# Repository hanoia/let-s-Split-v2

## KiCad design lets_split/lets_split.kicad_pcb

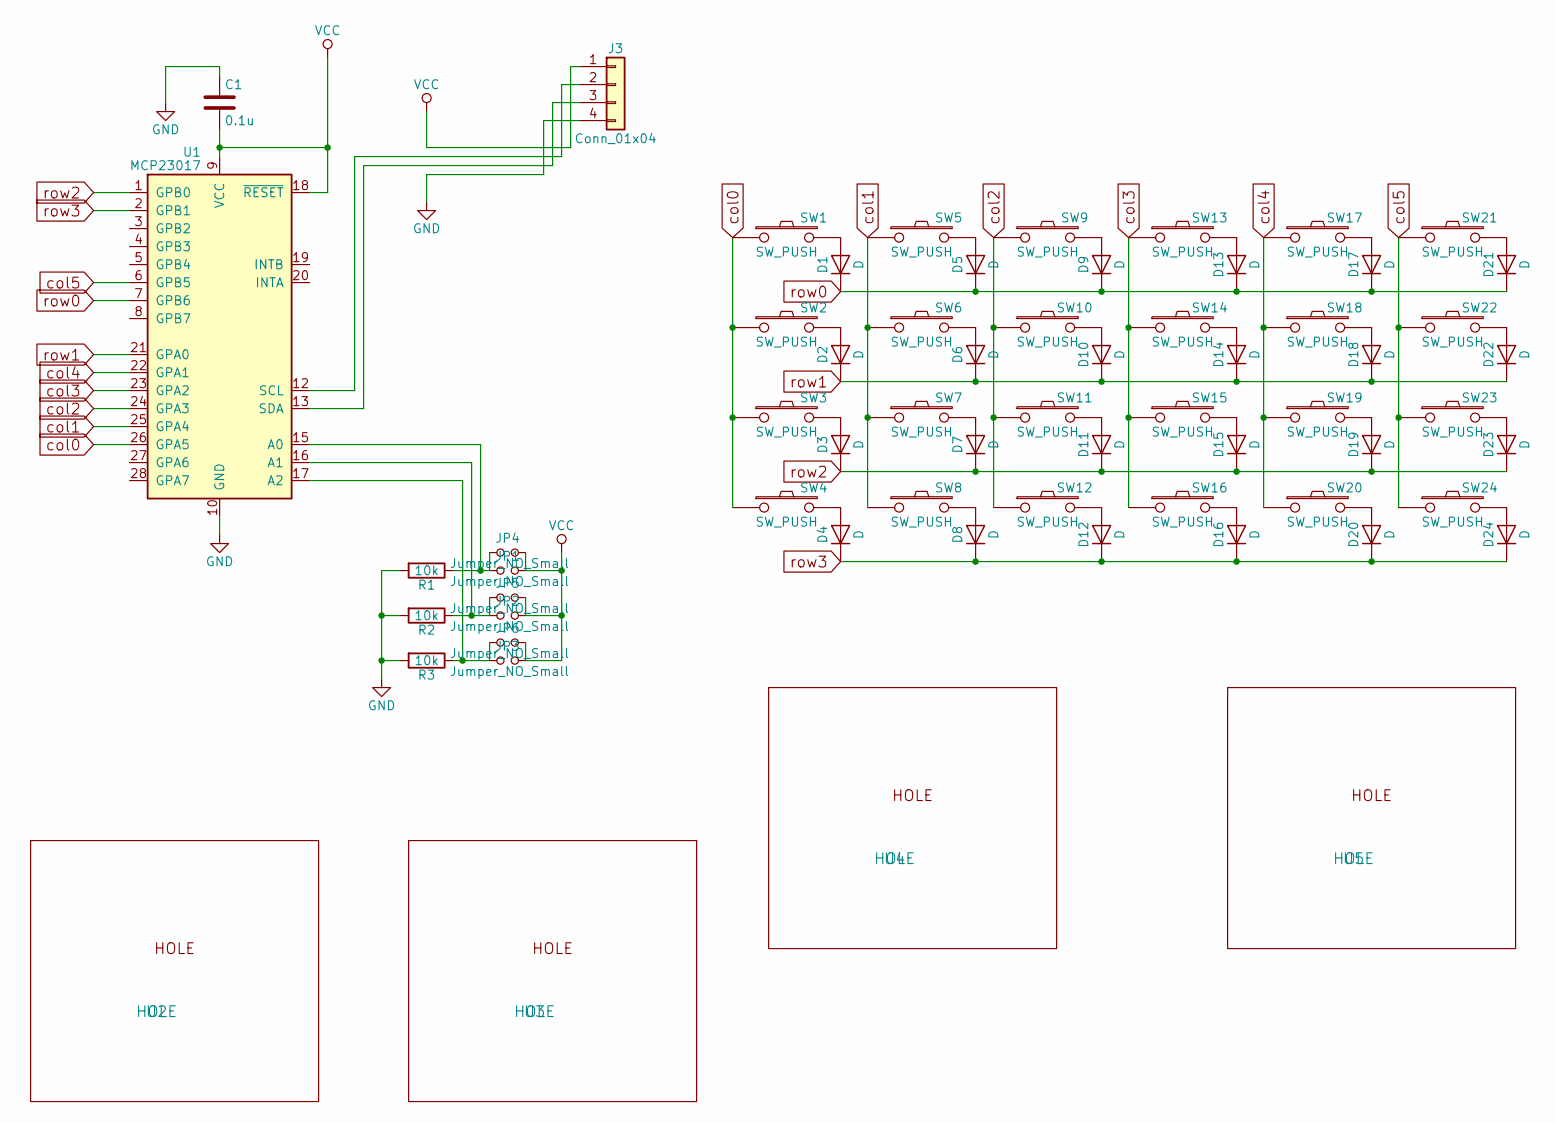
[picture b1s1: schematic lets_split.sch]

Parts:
C1: 0.1u; C_0603
D1, D2, D3, D4, D5, D6, D7, D8, D9, D10, D11, D12, D13, D14, D15, D16, D17, D18, D19, D20, D21, D22, D23, D24: D; D_SOD-123
J3: Conn_01x04; Pin_Header_Straight_1x04_Pitch2.54mm
JP1, JP2, JP3, JP4, JP5, JP6: Jumper_NO_Small; SolderJumper-2_P1.3mm_Open_Pad1.0x1.5mm
R1, R2, R3: 10k; R_0603
SW1, SW2, SW3, SW4, SW5, SW6, SW7, SW8, SW9, SW10, SW11, SW12, SW13, SW14, SW15, SW16, SW17, SW18, SW19, SW20, SW21, SW22, SW23, SW24: SW_PUSH; MXALPS_FLIP
U1: MCP23017; QFN-28-1EP_6x6mm_Pitch0.65mm
U2, U3, U4, U5: HOLE

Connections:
GND: C1.1, J3.4, R1.2, R2.2, R3.2, U1.10 (GND)
unnamed: D1.2 (A), SW1.2
unnamed: D2.2 (A), SW2.2
unnamed: D3.2 (A), SW3.2
unnamed: D4.2 (A), SW4.2
unnamed: D5.2 (A), SW5.2
unnamed: D6.2 (A), SW6.2
unnamed: D7.2 (A), SW7.2
unnamed: D8.2 (A), SW8.2
unnamed: D9.2 (A), SW9.2
unnamed: D10.2 (A), SW10.2
unnamed: D11.2 (A), SW11.2
unnamed: D12.2 (A), SW12.2
unnamed: D13.2 (A), SW13.2
unnamed: D14.2 (A), SW14.2
unnamed: D15.2 (A), SW15.2
unnamed: D16.2 (A), SW16.2
unnamed: D17.2 (A), SW17.2
unnamed: D18.2 (A), SW18.2
unnamed: D19.2 (A), SW19.2
unnamed: D20.2 (A), SW20.2
unnamed: D21.2 (A), SW21.2
unnamed: D22.2 (A), SW22.2
unnamed: D23.2 (A), SW23.2
unnamed: D24.2 (A), SW24.2
unnamed: J3.2, U1.12 (SCL)
unnamed: J3.3, U1.13 (SDA)
unnamed: JP1.1, JP4.1, R1.1, U1.15 (A0)
unnamed: JP2.1, JP5.1, R2.1, U1.16 (A1)
unnamed: JP3.1, JP6.1, R3.1, U1.17 (A2)
VCC: C1.2, J3.1, JP1.2, JP2.2, JP3.2, JP4.2, JP5.2, JP6.2, U1.9 (VCC), U1.18 (~RESET)
col0: SW1.1, SW2.1, SW3.1, SW4.1, U1.26 (GPA5)
col1: SW5.1, SW6.1, SW7.1, SW8.1, U1.25 (GPA4)
col2: SW9.1, SW10.1, SW11.1, SW12.1, U1.24 (GPA3)
col3: SW13.1, SW14.1, SW15.1, SW16.1, U1.23 (GPA2)
col4: SW17.1, SW18.1, SW19.1, SW20.1, U1.22 (GPA1)
col5: SW21.1, SW22.1, SW23.1, SW24.1, U1.6 (GPB5)
row0: D1.1 (K), D5.1 (K), D9.1 (K), D13.1 (K), D17.1 (K), D21.1 (K), U1.7 (GPB6)
row1: D2.1 (K), D6.1 (K), D10.1 (K), D14.1 (K), D18.1 (K), D22.1 (K), U1.21 (GPA0)
row2: D3.1 (K), D7.1 (K), D11.1 (K), D15.1 (K), D19.1 (K), D23.1 (K), U1.1 (GPB0)
row3: D4.1 (K), D8.1 (K), D12.1 (K), D16.1 (K), D20.1 (K), D24.1 (K), U1.2 (GPB1)

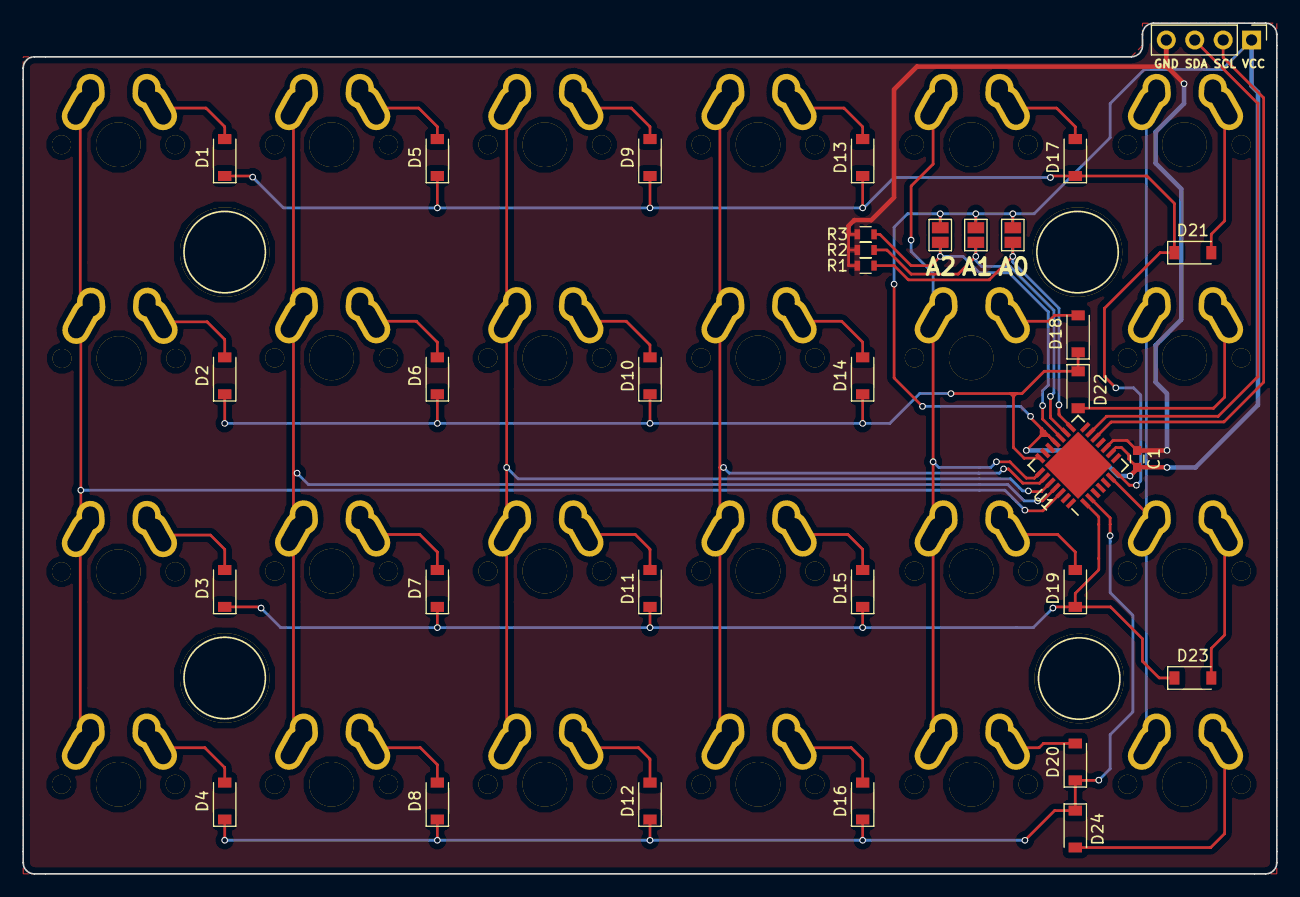
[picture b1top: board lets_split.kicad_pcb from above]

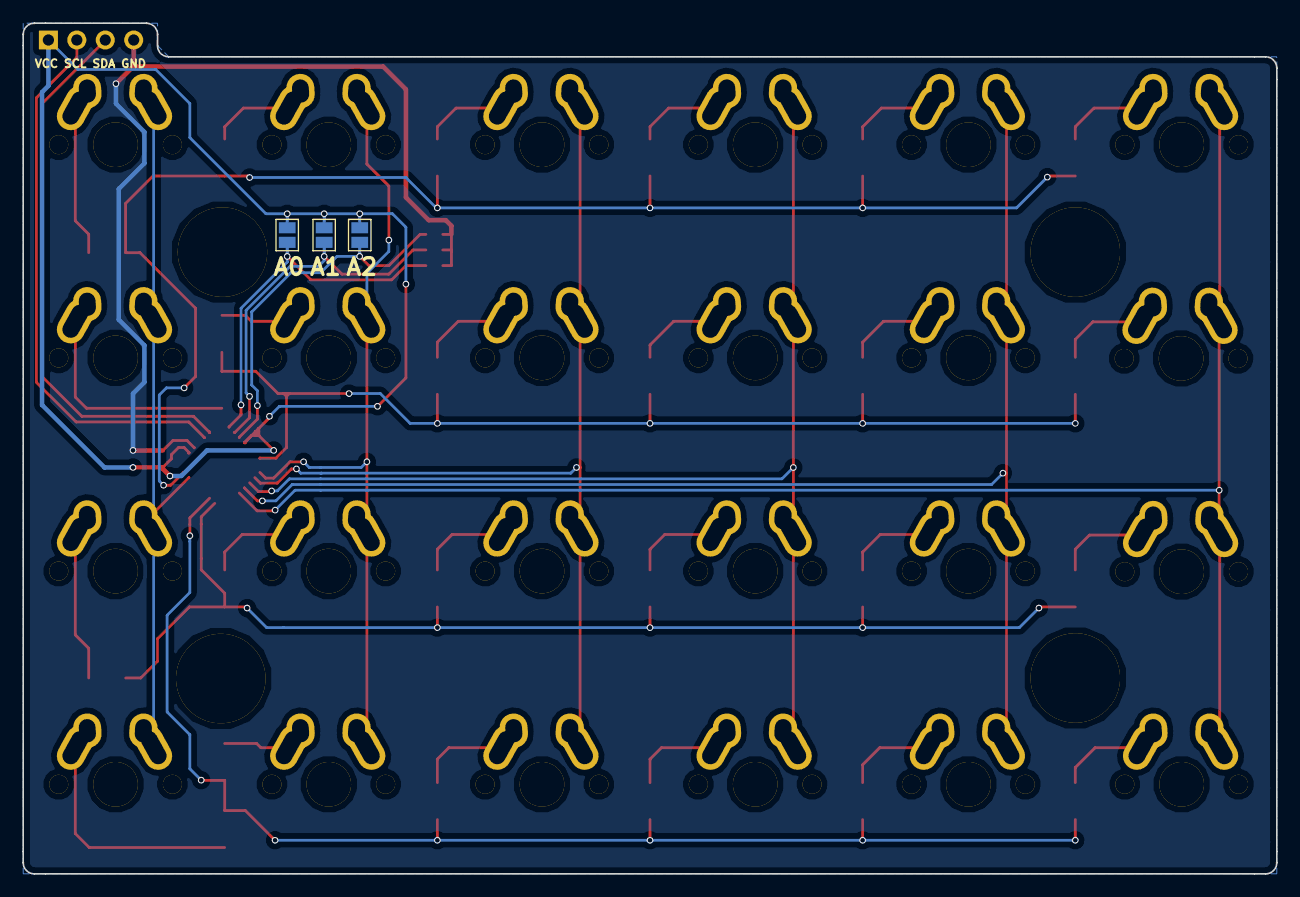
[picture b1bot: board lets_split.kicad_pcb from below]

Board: 2 copper layers, 112.0 x 76.0 mm, 64 parts (3 on the bottom side), 41 nets.

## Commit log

2018-04-10 Change controller ProMicro to MCP23017
